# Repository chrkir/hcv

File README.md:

# Viessmann Vitocal (E3) CAN-Bus to MQTT Bridge with Home Assistant Support

## Please also read the HCV Description in the docu folder.

An isolated, passive CAN-bus adapter to fetch local data from Viessmann E3-generation heat pumps (e.g., Vitocal 250-A, 252-A) and stream it via Wi-Fi to MQTT with native Home Assistant Auto-Discovery.

## 🚀 Key Features

- **100% Local Control:** No internet dependency, no official ViCare Cloud API rate limits.
- **Hardware Protection:** Features full galvanic isolation to protect your expensive heat pump from electrical damage.
- **Passive Sniffing:** Read-only operation ensures zero interference with the heating system's warranty.
- **Plug & Play for Home Assistant:** Built-in MQTT Discovery automatically creates all entities (temperatures, flow rates in L/h, energy in kWh, and states) without writing a single line of YAML.
- **Universal Compatibility:** Works seamlessly with Home Assistant, ioBroker, Node-RED, openHAB, and Symcon.

---

## 🔀 Supported Series & Target Selection (V200 vs. V250)

This project supports both the **E3 Generation (e.g., Vitocal 250-A, 252-A)** and the **V200/WO1C CAN Protocol (e.g., Vitocal 200-S, 200-A, HCV)** via dedicated software builds.

| Feature / Setting | Vitocal 250 (E3 Series) | Vitocal 200 (HCV / WO1C Series) |
| :--- | :--- | :--- |
| **Firmware Target** | Vitocal-250 Build | Vitocal-200 Build |
| **DID Profile File** | `vcalobj.did` | `vcalobj200.did` |
| **DID Format** | Decimal (e.g., `881`, `548`) | Hexadecimal (e.g., `0x0371`, `0x0100`) |
| **Log File** | `canLog250.txt` | `canLog200.txt` |
| **Bus Protocol** | E3 CAN Specification | WO1C CAN Variant |

---

### Selective DID Profile (`vcalobj200.did`) for Vitocal 200

When using the **Vitocal 200 Firmware**, the DID profile file must be uploaded as `vcalobj200.did`. Addresses correspond strictly to the WO1C / HCV hexadecimal address map:

```did
# ==============================================================================
# embdes Viessmann Vitocal 200 / WO1C Custom DID Profile
# Line comments starting with '#' are fully supported.
# ==============================================================================

# Core Temperatures & Controls (WO1C Hex Format)
{0x0100, OutdoorTemp, Aussentemperatur, 0, 1, FLOAT_TEMP_10},
{0x0371, OperatingMode, Betriebsart, 0, 1, INTEGER},
{0x0401, MixerPumpState, StatusMischerPumpe, 0, 1, ON_OFF},

```

## 🛠️ Project Structure & License Model

This project follows a hybrid **Open Hardware / Commercial Software** model to support the community while funding the extensive reverse-engineering work behind the Viessmann CAN protocols.

### 1. Open Hardware (Free)
All hardware files are open-source. You can find the schematics, PCB layout files (KiCAD/EasyEDA), Bill of Materials (BOM), and a 3D-printable enclosure STL file in the `/hardware` folder. Feel free to DIY and order your own boards.

### 2. Pre-Assembled Hardware (Optional)
If you do not want to solder SMD components or lack the equipment, you can buy a fully assembled and tested hardware unit inside its enclosure directly from me for **approx. €35 + MwSt ** (plus shipping from Germany). processDidData

### 3. Firmware & Software License
- **Demo Version (Free):** Includes the local Wi-Fi/MQTT captive portal captive setup, hardware connection test, and displays your unique ESP32 Chip ID.
- **Full Version (€48 + MwSt)** Unlocks all heating data points, daily energy counters, and native Home Assistant Auto-Discovery. It is a one-time payment per device and works **100% offline** (via a license file uploaded to the file system).

---

---

## 💻 Getting Started

### Hardware Connection
Connect the adapter to the **INTERNAL** CAN-bus of your Viessmann heat pump (typically labeled as "Plug 72" / Stecker 72 on the main terminal block). 

### Firmware Setup
1. Flash the free firmware build to your ESP32.
2. Power on the device and connect to the Wi-Fi Access Point generated by the adapter.
3. Open `http://192.168.1.1` in your browser, enter your local Wi-Fi and MQTT broker credentials.
4. Copy the unique **Chip ID** shown on the web interface.

### Activating the Full Version
To unlock all sensors and Home Assistant Auto-Discovery:
1. Reach out to me via **PM in the Forums** or via Email at `info@embdes.com` with your **Chip ID**.
2. After payment (€50), you will receive a `license.txt` file.
3. Upload this file through the adapter's web interface and reboot the device.
4. Open Home Assistant ➔ **Settings** ➔ **Devices & Services** ➔ **MQTT**—your heat pump will show up automatically!

---

## 📊 Supported Data Points (Extract)

- **Analogue Sensors:** Flow/Return temperatures, Outdoor temperature, Domestic Hot Water (DHW) temp, Compressor frequency.
- **Flowrates:** Allengra Sensor / Volumetric flow rate (properly formatted in `L/h`).
- **Energy Dashboard:** Daily energy consumption (properly formatted in `kWh` with `total_increasing` state class).
- **Binary States:** Compressor status, Mixer pump status, Error flags (formatted with native `running` and `problem` device classes).

---

## ⚙️ Customizing Data Points (Selective DIDs)

By default, the adapter processes all available data points. To keep your MQTT broker clean and reduce network traffic, you can now upload a custom selection profile via a `vcalobj.did` file through the web interface. 

Only the DIDs specified in this file will be active on the CAN bus, transmitted via MQTT, and displayed in the local web app.

### CAN Bus Logging
* Integrated CAN bus logging to record and analyze raw network traffic.
* Supports capturing all bus messages or filtering by specific CAN IDs to easily discover and map new DIDs for custom MQTT messages.

### Data Identifier (DID) Management & Web Interface
* Structured handling and parsing of Data Identifiers (`vcalobj.did`).
* Responsive Web UI featuring dedicated help text styling to cleanly separate parameter descriptions from real-time sensor data.

### File Format (`vcalobj.did`)

The file must be uploaded as a plain text or CSV-like format using the following structure:
`{ID, Description_Original, Description_Custom, Byte_Position, Display_Flag, DID_TYPE}`

Here is a verified example for a minimal setup (Core temperatures, flowrate, and energy counters).

**Note:** New releases may expand the configuration; the file itself is always the source of truth.

```did
# ==============================================================================
# embdes Viessmann E3 Custom DID Profile
# Remove or add rows to customize your MQTT payload and local dashboard.
# Line comments starting with '#' are fully supported.
# ==============================================================================

# Core Temperatures
{268, FlowTemperatureSensor, Vorlauftemperatur, 0, 1, FLOAT_TEMP_10},
{269, "ReturnTemperatureSensor", "AußeneinheitRücklauftemperatur", ...},
{271, DomesticHotWaterSensor, WarmwasserTemperatur, 0, 1, FLOAT_TEMP_10},
{274, OutdoorTemperatureSensor, Aussentemperatur, 0, 1, FLOAT_TEMP_10},

# Flowrate & Hydraulics
{1043, VolumetricFlowrateSensor, DurchflussSensorStd, 0, 1, FLOAT_LH},

# Energy Dashboard
{548, EnergyConsumptionPerDay, EnergieaufnahmeProTagInKWh, 0, 1, P_KWH},

# Binary States (On/Off)
{401, MixerPumpStatus, StatusMischerPumpe, 0, 1, ON_OFF},
```

### ⚠️ Critical Formatting Rules

To avoid parsing errors on the microcontroller, ensure your `vcalobj.did` strictly adheres to these rules:

1. **No trailing spaces before commas:** Ensure numeric values do not contain spaces before a comma (e.g., use `1,` instead of `1 ,`).
2. **Entity naming:** Avoid special characters like `%` within the custom description strings. Use clean alphanumeric names (e.g., `LuefterEinsDrehzahl` instead of `LuefterEinsDrehzahl%`).
3. **Valid Data Types:** Supported `DID_TYPE` tokens are:
   - `FLOAT_TEMP_10`, `FLOAT_PRES_10`, `FLOAT_PRES_100`
   - `ON_OFF`, `INT_TIME`, `INT_PERC`, `P_KWH`, `P_WATT`
   - `FLOAT_LH`,  `INTEGER`

### How to apply changes

1. Create or edit your `vcalobj.did` file using a standard text editor (like VS Code or Notepad++).
2. Open the adapter's web interface in your browser.
3. Navigate to the **File Upload** section, select your `vcalobj.did` file, and hit upload.
4. The adapter will validate the file, save it to the internal flash storage, and dynamically reload the database into RAM without needing a manual hardware reset.

## 🚗 Integration with evcc (PV Charging Manager)

The embdes adapter can be integrated into [evcc](https://evcc.io) as a passive **heat pump power meter**. Since the adapter operates strictly in **read-only mode**, it is 100% safe and will not interfere with your Viessmann warranty.

To display your heat pump's consumption in evcc, add the following configuration to your `evcc.yaml`:

```yaml
meters:
  - name: viessmann_heatpump
    type: custom
    power:
      source: mqtt
      topic: viessmann/wp/state
      jq: .EnergieaufnahmeProTagInKWh oder EnergyConsumptionCentralHeating # Fetches the daily energy counter from the JSON payload
```

*Note: The adapter acts as a pure data provider (Push-to-MQTT). No active HTTP polling or writing to the CAN-bus is required or supported.*

---

## Web UI Parameter Control (Write Support)

Starting with **v1.14.0**, the HCV Web Interface allows you to adjust parameters directly on the Vitocal 250 heating unit without needing external automation scripts or manual MQTT commands.

### Key Features:
* **Direct Web Control:** Click on writable parameters within the dashboard to bring up the interaction dialog.
* **Safety & Boundary Checks:** Displays allowed minimum and maximum boundaries (e.g., `Min: 10 | Max: 60` for `WarmwasserSolltemperaturNormal`) defined by `vcalobj.did` to prevent invalid inputs.
* **DID Transparency:** Clearly displays the active Data Identifier (e.g., `DID: 0x18C`).
* **Instant Bus Dispatch:** Clicking **Senden** formats and transmits the updated setpoint straight to the Vitocal CAN bus.

---
<br><br><br>

# 🛠️ Changelog & What's New
<br>

## Release V1.49 – Fix for broken DID control in Release 1.48

# sorry for the inconvenience

## Release V1.48 – Multi-Adapter Support & Memory Alignment Fixes & Maintenace updates

### New Features & Enhancements

* **Multi-HCV Support (Multi-Device Networking):**  
  Introduced the configurable `Device Id` field (Default: `HCV`). Enables running multiple HCV adapters concurrently on the same MQTT broker without topic overlapping or Home Assistant entity collisions.

* **Dynamic Home Assistant Discovery & Topic Mapping:**  
  The `deviceId` dynamically maps into Home Assistant Discovery payloads (`uniq_id`, `dev.ids`, entity names) as well as base MQTT publish/subscribe topics.

* **Configuration Backup and Restore:**
  Restructured "Einstellungen" into a sub-dropdown menu (`Optionen`, `Konfiguration sichern`, `Konfiguration laden`) to allow the HCV-Configuration Data to save and restore from local PC.

---

### Bug Fixes & Stability Improvements

* **Memory Alignment & CPU Panic Fix:**  
  Resolved hardware exception crashes on Xtensa LX6 architecture caused by unaligned 32-bit access in packed structures (`enabledCategories`, IP address fields).

* **MQTT Payload Null-Termination:**  
  Ensured proper string null-termination (`\0`) on all incoming MQTT payloads prior to logging or execution routines.

* **CAN Port 91 (PV/VX3) DID Isolation:** Fixed `loadVcalObjDat()` active mask logic. Selecting Port 91 now strictly isolates `CAT_PV_VX3` (0x0040) objects, preventing baseline heat pump DIDs from loading.

* **RAM Object Reset:** Added `memset` array clearing in `loadVcalObjDat()` prior to DID parsing to prevent stale default DIDs from persisting in RAM.

* **Active Polling:** Fixed condition evaluation in the VX3 polling task for active request frames on CAN ID `0x441`.

* **CAN-ID Filter Fix (0x690 → 0x451):** In previous firmware versions (including V1.43), canMsgHandler and the smart polling task incorrectly filtered for CAN-ID 0x690.

* **Impact:** UDS diagnostic responses from the Vitocharge VX3 / auxiliary CAN on Plug 91 are transmitted on CAN-ID 0x451 (as positive responses to requests sent to 0x441). The invalid filter caused incoming VX3 payload frames to be discarded and broke passive master detection.

---

### 📑 Migration & Upgrade Instructions

1. **OTA Update:** Flash the `v1.45` binary via Web-UI or PlatformIO OTA.
2. **Single Adapter Setup:** No action required. The adapter boots with default `deviceId` (`Vitocal-CAN`) and resumes standard operation.
3. **Multi-Adapter Setup:**
   * Open the web interface (`http://<ADAPTER_IP>/options`).
   * Update **Device ID** to a unique identifier (e.g., `Vitocal-EG`, `Vitocal-OG`).
   * Click **Save & Reboot**.

## Release v1.41 – Smart Connector Assignment, Transparent VX3 DID Allocation & Ethernet Rescue Mode

This release introduces a streamlined, connector-driven DID management architecture, transparent Vitocharge VX3 integration, and solidifies the Early-Boot Ethernet Rescue Mode for reliable recovery.
**What’s New in v1.41**
* Smart Connector-Driven DID Assignment
    Connector Selection: Added a dedicated CAN Connector dropdown (Stecker 72 vs. Stecker 91) in the Web UI (/options).
  * Stecker 72 (Internal Refrigerant Circuit CAN): Tailored for local heat pump sensors & circuit modules.
  * Stecker 91 (System CAN Bus): Used for system-wide metrics and external device integration.

    Dynamic UI Form Adaptation: Selecting Stecker 91 automatically hides module-specific checkboxes (Heizkreis 1–3, DHW, Buffer) in the frontend to prevent invalid or conflicting configuration options.

* Transparent Vitocharge VX3 / PV Integration
  * Removed UI Clutter: The standalone VX3 / c_pv checkbox has been removed from the frontend UI.
  * Unified Object Storage: Vitocharge VX3 DIDs are now natively embedded within the core /vobjects.dat file.
  * Automatic Backend Activation: When Stecker 91 is selected, the firmware automatically injects the CAT_VX3 bit (0x0040 / Bit 64) into the active object bitmask (activeMask) during loadVcalObjDat(). PV, battery, and inverter metrics are loaded seamlessly without requiring user intervention.

* Early-Boot Ethernet Rescue Mode (Hot-Plug Recovery)
  * Deterministic Network Modes: Strict separation between Ethernet (netMode = 0) and Wi-Fi (netMode = 1). No unexpected fallback switching.

    Bootloop & Freeze Prevention: If a corrupted or oversized custom .did file prevents the device from starting, trigger the rescue mode via hot-plug:

        Unplug the Ethernet cable.

        Power-cycle the HCV module.

        Re-plug the Ethernet cable within 10 seconds of cold boot.

    Safe Recovery Environment: The device enters Rescue Mode ([http://hcv.local](http://hcv.local) and Telnet on Port 23). Custom user DID files (/uobjects.dat) are completely bypassed, allowing web/FTP/Telnet access to delete or repair damaged files.

## Release v1.38

Comprehensive stability update focusing on Wi-Fi connection resilience, LwIP stack crash prevention, and UI setup flexibility.

## Key Improvements & Fixes

* **Active Wi-Fi Watchdog & Auto-Recovery:**
  * Integrated background monitoring for Wi-Fi connection state.
  * Periodically retries connection every 15 seconds if disconnected.
  * Triggers an automatic system reboot (`ESP.restart()`) after 5+ minutes of continuous disconnection (e.g., during night-time router/repeater reboots) to guarantee clean re-association with the AP.

* **Deterministic Network Mode:**
  * **Ethernet Mode:** PHY initializes on boot and strictly waits for cable connection and DHCP IP lease. Prevents unintended fallback to Wi-Fi. Supports hot-plugging.
  * **Wi-Fi Mode:** Connects strictly to the configured Wi-Fi network.

* **LwIP Stack & Crash Prevention (`mbox` Fix):**
  * Optimized initialization sequence in `startNetwork()`.
  * `WiFi.mode(WIFI_STA)` is invoked at the very start to ensure LwIP mailboxes and tasks are fully operational before launching CAN bus tasks, WebServer, or MQTT sockets.

* **Flexible Wi-Fi Pre-Configuration (Web UI):**
  * Replaced static select dropdown with a free-text `<input>` linked to an HTML5 `<datalist>`.
  * Allows manual SSID entry in Ethernet mode to pre-configure Wi-Fi credentials without requiring an active Wi-Fi scan.

---

### Release v1.33
* **Added:**&emsp; Expanded Telnet terminal functions and command handling for remote diagnostics.
* **Added:**&emsp; Dedicated logging for MQTT connection status and WiFi disconnect reason codes.
* **Improved:**&emsp; Enhanced WiFi stability and compatibility with modern routers (PMF handling & disabled modem-sleep).
* **Improved:**&emsp; Reliability of NTP time synchronization across network interfaces.
* **Fixed:**&emsp; Cold-boot panic crash (`ESP_RST_PANIC`) during W5500 Ethernet initialization with plugged cable.
* **Fixed:**&emsp; Byte-alignment offset issue causing incorrect IP address rendering ("IP address all equal").
* **Fixed:**&emsp; Telnet session lifecycle and socket handling for the Ethernet variant.
* **Fixed:**&emsp; Relative boot timestamp calculations and log message update frequency.

### 🆕 New: HCV Ethernet & WLAN Edition - Release 1.30

In addition to the Wi-Fi-only version, the **HCV Ethernet Edition** is now available.

* 🔌 **Dual Connectivity (LAN & Wi-Fi):** Connect either via a standard RJ45 Ethernet network cable or Wi-Fi.
* 📶 **Ideal for Basement Installations:** Maximum stability and reliability – even in utility rooms with poor Wi-Fi reception.
* ⚡ **Same Full Feature Set:** Full support for all CAN data points, Home Assistant Auto-Discovery, and 100% cloud-free local operation.

### Release v1.29
* **Fixed:** Resolved issue with Access Point (AP) mode selection.
* **Fixed:** Fixed main page rendering and display issues in Google Chrome browsers.
* **Fixed:** Corrected DID access for CAN ID `0x693` (Display Unit).
* **Added:** Password visibility toggle in the WebUI configuration panel.

### Hardware 1.6
* **Changed CAN Line protection**

### Release v1.25 – Dynamic VX3 DID Engine & Multi-Mode Support
### 🚀 Key Improvements & Features
* **Dedicated `vx3obj.did` Table File:** Fully decoupled VX3 data points from the standard Vitocal table (`vcalobj.did`).
* **Three Flexible Operating Modes:**
  1. **Heat Pump Only (without VX3):** Standard operating mode for standalone Vitocal heat pump systems.
  2. **Heat Pump + VX3:** Combined mode to read data from both the heating system and the PV/battery storage.
  3. **VX3 Only (without Heat Pump):** Dedicated mode for standalone Vitocharge storage/inverter installations.
* **Enhanced DID Engine (v1.25 / v1.24):** Fully dynamic decoding for all payload sizes (1, 2, and 4 bytes) including Big-Endian processing, signed power values (charge/discharge), and 32-bit multi-frame UDS responses (e.g., grid feed-in/consumption meters like DID 535).

### 📜 Changelog Summary (v1.22 – v1.25)
* **v1.25:** Improved VX3 mode detection and web display logic.
* **v1.24:** Added 32-bit integer handling (P_KWH / P_WATT) and improved sign/endianness processing.
* **v1.23:** Removed page refresh flicker on `httpMain`, corrected write-filter logic (`writeFlg`) for read-only sensor points, and added new VX3 configuration options in the Web UI.
* **v1.22:** Added dedicated VX3 data handler (active & passive mode), introduced `vx3obj.did` file, and fixed `vcalobj.did` mappings (corrected DID 534/535 to 526/528).

### Enhancements (v1.21)
* **Multi-Frame DID Support:** Added ISO-TP multi-frame decoding support for long DIDs spanning multiple CAN messages. 

### Bug Fixes & Stability (v1.20)
* **Critical Wi-Fi Auto-Connect Fix:** Corrected WiFi.begin() parameter passing in auto-select mode, resolving connection issues when BSSID lock is unused.
* **Wi-Fi 6 (802.11ax) Support:** Explicitly enabled 802.11ax protocol support on ESP32-C6 targets (TARG_V250_C6) to prevent connection timeouts on Wi-Fi 6 routers (e.g., FRITZ!Box AX).
* **AP Mode Wi-Fi Scanning:** Configured AP mode to run in dual WIFI_AP_STA mode to allow asynchronous scanning of nearby networks during setup.
* **Watchdog Stability (TWDT Fix):** Offloaded OTA reboot and factory reset operations from the async_tcp task context to prevent Task Watchdog resets.

### New Features & UI Enhancements
* **SSID Selection Dropdown:** Populates nearby Wi-Fi SSIDs with signal strength indicators (dBm) directly from the scan cache.
* **Web UI Factory Reset:** Added factory reset trigger into the setup dropdown menu (accessible exclusively in AP mode with safety prompt).
* **Clean UI Formatting:** Improved active SSID dropdown rendering.

### 🐛 Bug Fixes & Refinement (v1.19)
* **CAN Data Display:** Fixed an issue introduced in v1.18 where CAN data was not displaying correctly in the interface.
* **DID Integer Display:** Fixed false DID value formatting and display for integer units.

### 🌐 MQTT & System Stability (v1.18)
* **Home Assistant Auto-Discovery:** Fixed HA Discovery functionality upon MQTT reconnect, including proper handling of retained messages.
* **Boot State Display:** Set default DID value display to `--` right after HCV boot until valid data is received.
* **DID Object Management:** Fixed automatic reloading of DID objects immediately after a new file upload.
* **Wi-Fi Auto-Reconnect:** Improved Wi-Fi reconnect mechanism by resetting the Wi-Fi channel after a timeout event.

### ⚙️ System Control & Network Configuration (v1.16 – v1.17)
* **Global Reset:** Added a global system reset function with safe CAN bus deinitialization (`can deinit`).
* **Wi-Fi Manager:** Reworked Wi-Fi configuration with integrated Access Point (AP) selection.

---

## ⚠️ Upgrade Note
If you are upgrading from v1.18, updating to **v1.19.0** is strongly recommended to resolve the CAN data display issue.

## ✉️ Contact & Support

If you want to buy a pre-assembled board or a software license, please contact me:
- **Home Assistant Forum:** [@chrkir](https://home-assistant.io)
- **ioBroker Forum:** [@chrkir](https://iobroker.net)
- **Email:** `info@embdes.com`

*Disclaimer: This is a third-party community project. This project is not affiliated with, authorized, or endorsed by Viessmann.*

## Links & Resources

- [GitHub Repository](https://github.com/chrkir/hcv)
- [Dokumentation](https://github.com/chrkir/hcv/tree/main/docu)
- [Hardware Ordner](https://github.com/chrkir/hcv/tree/main/hardware)
- [Software Ordner](https://github.com/chrkir/hcv/tree/main/software)

### Update-Info: Modulare DID-Auswahl & Einbindung eigener DIDs

Dieses Update passt die DID-Verarbeitung im HCV-Adapter direkt an die individuelle Ausstattung der jeweiligen Vitocal-Anlage an.

---

#### 1. Abbildung der eigenen Vitocal-Konfiguration

Die zentrale DID-Tabelle (`vcalobj.did`) deckt verschiedene Anlagentypen und Erweiterungen ab. Über das Web-Interface unter **Optionen** lässt sich die Konfiguration exakt auf die tatsächlich verbauten Komponenten einstellen:

* **[BASE]**: Grundfunktionen (Außentemperatur, Vorlauf, Systemdruck, Verdichter)
* **[HK1] / [HK2] / [HK3]**: Heiz- und Mischerkreise
* **[DHW]**: Warmwasserbereitung und Zirkulation
* **[BUFFER]**: Pufferspeicher
* **[PV_VX3]**: Photovoltaik & Vitocharge VX3
* **[SOLAR]**: Solaranlage

**Ablauf:** Im Web-Interface werden nur die Haken bei den Modulen gesetzt, die in der eigenen Heizung vorhanden sind. Der Adapter liest daraufhin ausschließlich diese Datenpunkte in den Speicher ein.

---

#### 2. Eigene DIDs und Update-Sicherheit (`user.did`)

Um eigene Anpassungen bei Updates der Standard-Tabelle nicht zu verlieren, ist die Konfiguration getrennt:

* **Standard-Datei (`vcalobj.did`)**: Enthält die vom Adapter mitgelieferten Viessmann-DIDs.
* **Eigene Datei (`user.did`)**: Enthält benutzerdefinierte DIDs in der Sektion `[USER]`.

Beim Aktualisieren der `vcalobj.did` bleibt die `user.did` auf dem Gerät erhalten. Der Adapter lädt beim Start die ausgewählten Standard-Sektionen und hängt die Einträge aus der `user.did` an.

---

#### 3. Funktionsweise im Hintergrund

* **Upload:** Beim Hochladen einer `.did`-Datei wird der Inhalt einmalig in eine Binärdatei auf dem Gerät umgewandelt (`/vobjects.dat` bzw. `/uobjects.dat`).
* **Systemstart:** Das zeilenweise Einlesen und Zerlegen von Textzeilen entfällt. Der Adapter lädt die gefilterten Datenblöcke direkt in den Arbeitsspeicher.

---

### Kurzanleitung zur Einrichtung

1. `vcalobj.did` im Web-Interface hochladen.
2. Unter **Optionen** die Sektionen aktivieren, die in der eigenen Vitocal verbaut sind.
3. Eigene DIDs (falls vorhanden) in der Datei `user.did` unter `[USER]` ablegen und hochladen:
```ini
[USER]
{ 9999, "CustomSensor", "Mein_Eigener_Wert", 0, FLOAT_TEMP_10, 0, 0, 0x680, 1, 0, 2 }

```

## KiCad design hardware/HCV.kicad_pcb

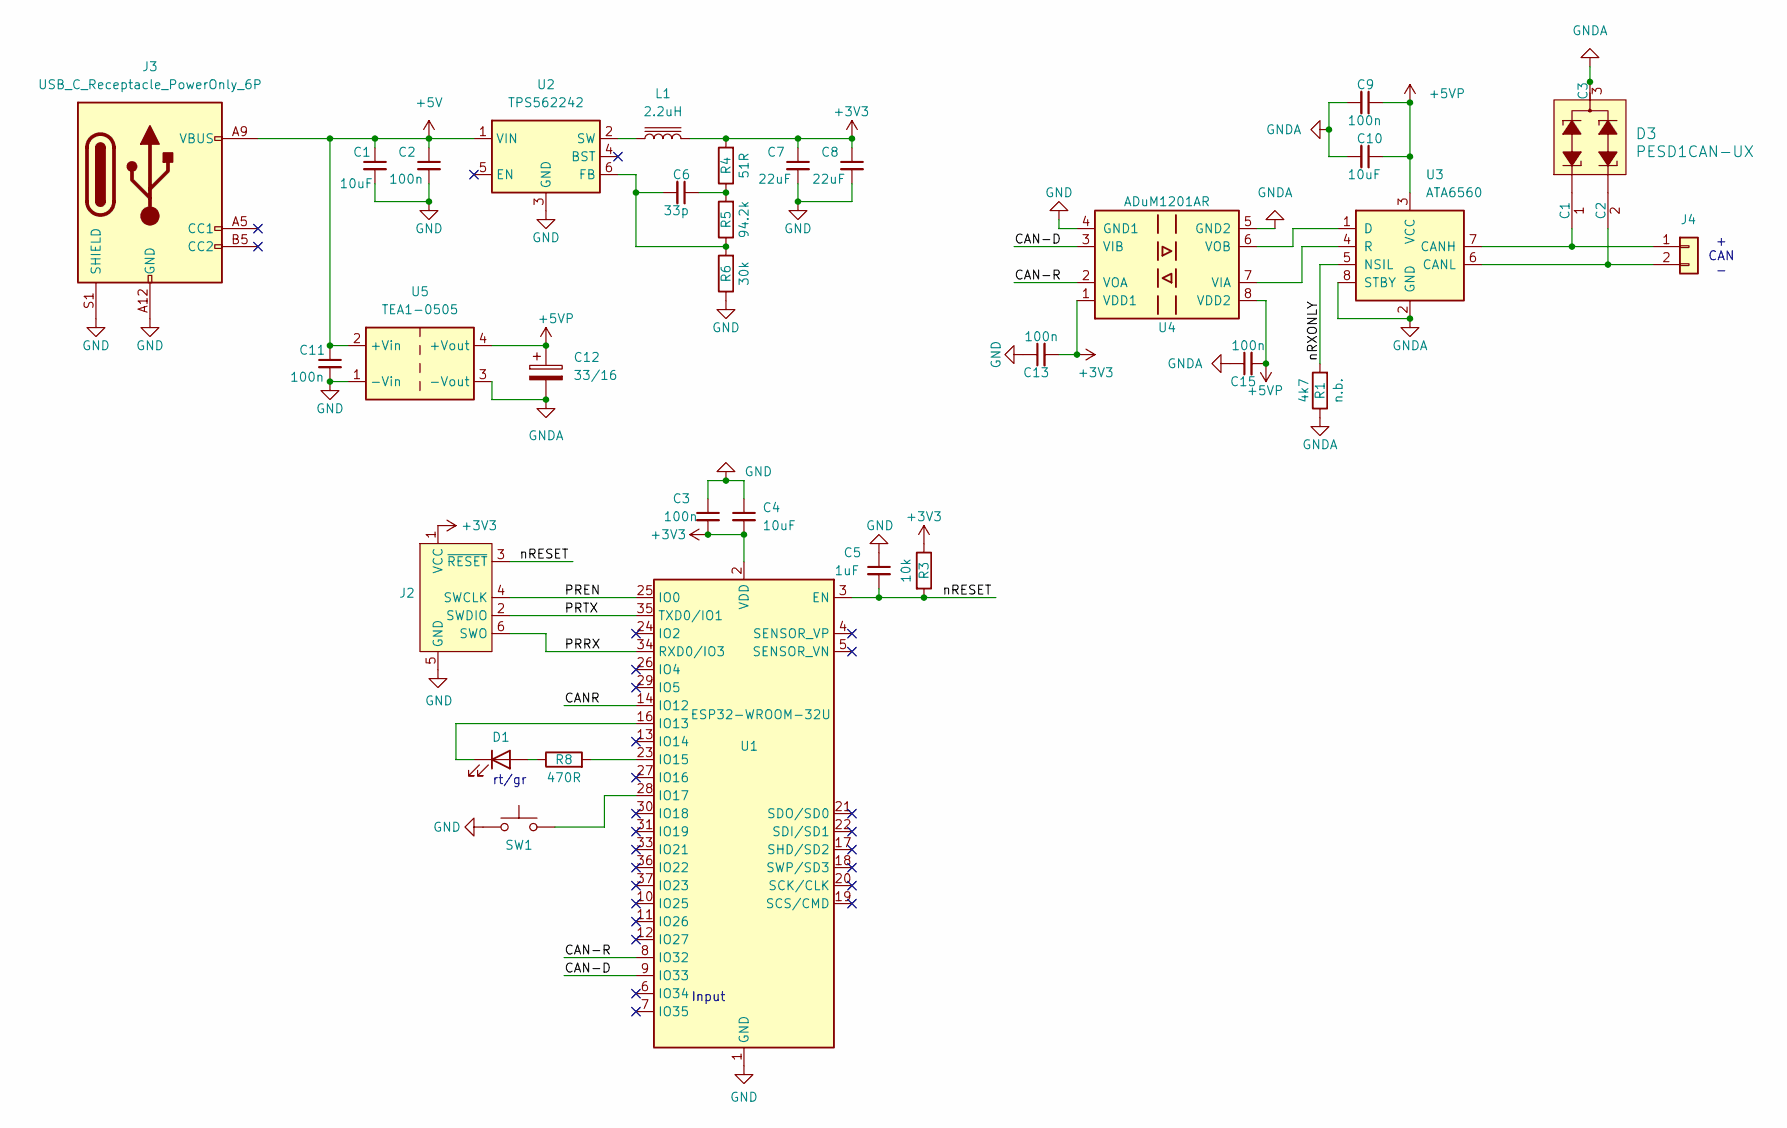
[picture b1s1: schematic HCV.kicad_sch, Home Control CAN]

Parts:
C1, C4, C10: 10uF; C_0805_2012Metric
C2, C3, C9, C11, C13, C15: 100n; C_0603_1608Metric
C5: 1uF; C_0603_1608Metric
C6: 33p; C_0603_1608Metric
C7, C8: 22uF; C_1206_3216Metric_Pad1.33x1.80mm_HandSolder
C12: 33/16; CP_EIA-3528-12_Kemet-T
D1: LED; LED_D3.0mm
D3: PESD1CAN-UX; SOT-23-3; MPN PESD1CAN-UX; Digi-Key_PN 1727-1306-1-ND
J2: Conn_ARM_SWD_TagConnect_TC2030; Tag-Connect_TC2030-IDC-FP_2x03_P1.27mm_Vertical
J3: USB_C_Receptacle_PowerOnly_6P; USB_C_Receptacle_GCT_USB4125-xx-x-0190_6P_TopMnt_Horizontal
J4: Conn_01x02; PhoenixContact_MC_1,5_2-G-3.5_1x02_P3.50mm_Horizontal
L1: 2.2uH; L_Bourns-SRN4018
R1: 4k7; R_0603_1608Metric
R3: 10k; R_0603_1608Metric
R4: 51R; R_0603_1608Metric
R5: 94.2k; R_0603_1608Metric
R6: 30k; R_0603_1608Metric
R8: 470R; R_0603_1608Metric
SW1: SW_Push; SW_SPST_EVPBF
U1: ESP32-WROOM-32U; ESP32-WROOM-32
U2: TPS562242; SOT-563
U3: ATA6560; SOIC-8_3.9x4.9mm_P1.27mm
U4: ADuM1201AR; SOIC-8_3.9x4.9mm_P1.27mm
U5: TEA1-0505; Converter_DCDC_TRACO_TEA1-xxxx_THT

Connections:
+3V3: C3.2, C4.2, C7.1, C8.1, C13.2, J2.1 (VCC), L1.2, R3.1, R4.2, U1.2 (VDD), U4.1 (VDD1)
+5V: C1.1, C2.1, C11.1, J3.A9 (VBUS), J3.B9 (VBUS), U2.1 (VIN), U5.2 (+Vin)
+5VP: C9.1, C10.1, C12.1, C15.2, U3.3 (VCC), U4.8 (VDD2), U5.4 (+Vout)
/CAN-D: U1.9 (IO33), U4.3 (VIB)
/CAN-R: U1.8 (IO32), U4.2 (VOA)
/CANR: U1.14 (IO12)
/PREN: J2.4 (SWCLK), U1.25 (IO0)
/PRRX: J2.6 (SWO), U1.34 (RXD0/IO3)
/PRTX: J2.2 (SWDIO), U1.35 (TXD0/IO1)
/nRESET: C5.2, J2.3 (~RESET), R3.2, U1.3 (EN)
/nRXONLY: R1.2, U3.5 (NSIL)
GND: C1.2, C2.2, C3.1, C4.1, C5.1, C7.2, C8.2, C11.2, C13.1, J2.5 (GND), J3.A12 (GND), J3.B12 (GND), J3.S1 (SHIELD), R6.1, SW1.1, U1.1 (GND), U1.15 (GND), U1.38 (GND), U1.39 (GND), U2.3 (GND), U4.4 (GND1), U5.1 (-Vin)
GNDA: C9.2, C10.2, C12.2, C15.1, D3.3 (C3), R1.1, U3.2 (GND), U3.8 (STBY), U4.5 (GND2), U5.3 (-Vout)
unnamed: C6.1, R4.1, R5.2
unnamed: D1.2 (A), R8.1
unnamed: D1.1 (K), U1.16 (IO13)
unnamed: D3.1 (C1), J4.1, U3.7 (CANH)
unnamed: D3.2 (C2), J4.2, U3.6 (CANL)
unnamed: R8.2, U1.23 (IO15)
unnamed: SW1.2, U1.28 (IO17)
unnamed: C6.2, R5.1, R6.2, U2.6 (FB)
unnamed: L1.1, U2.2 (SW)
unnamed: U3.1 (D), U4.6 (VOB)
unnamed: U3.4 (R), U4.7 (VIA)

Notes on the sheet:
rt/gr
+ CAN -
Input

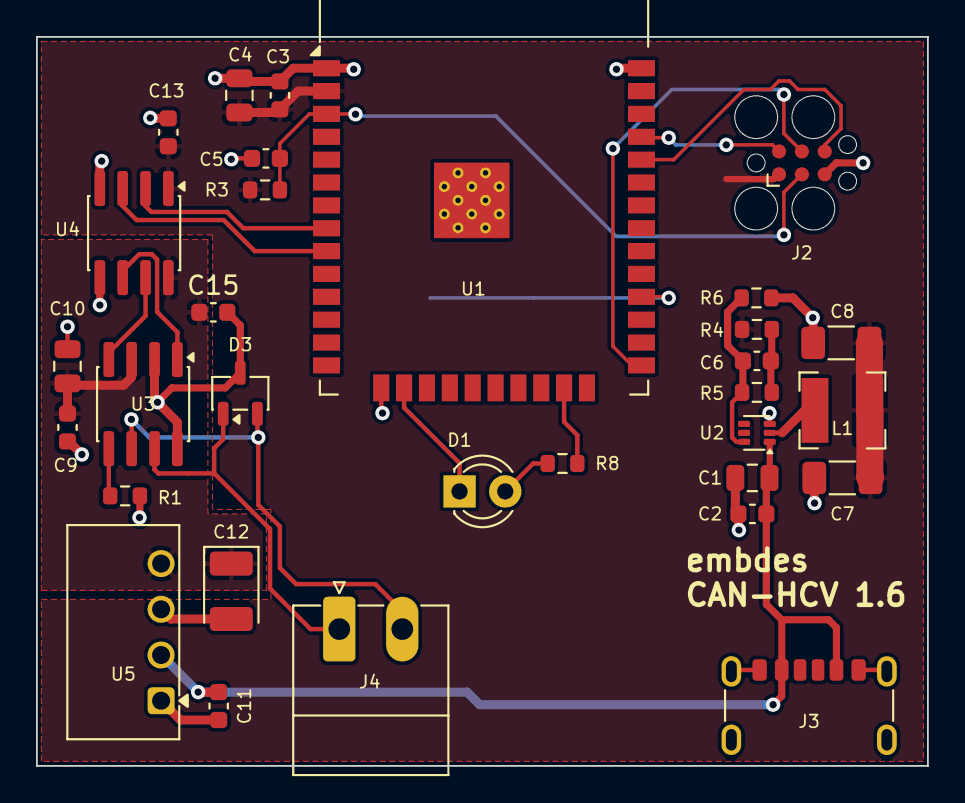
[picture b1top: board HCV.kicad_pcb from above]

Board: 2 copper layers, 49.5 x 40.5 mm, 32 parts (1 on the bottom side), 23 nets.

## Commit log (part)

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2026-06-14 Added descrption file
2026-06-14 Added iobroker object
2026-06-15 removed picture
2026-06-15 updated docu
2026-06-16 Docu update
2026-06-24 Added Hardware and Software
2026-06-27 Updated Docu, Updated Hardware
2026-06-30 Updated SW to relase 0.88 with coustomized data points
2026-06-30 fixed readme.md
